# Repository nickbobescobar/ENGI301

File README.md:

# ENGI301
Repository for ENGI 301 coursework

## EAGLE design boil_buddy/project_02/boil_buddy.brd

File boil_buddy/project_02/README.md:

--------------------------------------------------------------------------
Boil Buddy: Text message alerts for a boiling pot of water
--------------------------------------------------------------------------
Copywright 2020 Nicolas Escobar
nick[dot]bob[dot]escobar[at]gmail[dot]com

This is the Boil Buddy PCB Design! Boil Buddy uses a piezoelectric disc to sense vibrations in the pot as water boils and sends a text alert.
This PCB was adapted from a PocketBeagle project and thus makes use of many chips found on that board, including the Octavo Systems OSD353558 Microprocessor.
In converting to the PCB design, my goal was to eliminate extraneous components from the PocketBeagle to cut down on costs and size. However, I learned that
the PocketBeagle doesn't really have much that I don't need built into it (unless I swap the CPU) and that it would be *much* more cost-efficient to make a shield
for the existing board.

The 'boil_buddy' folder on GitHub should contain software used to run the Boil Buddy, at least for the prototyped version. I'm unsure on how to adapt it to a
standalone device, though I figure that I'd be using much of the same Debian backbone because I've kept most of the same hardware.

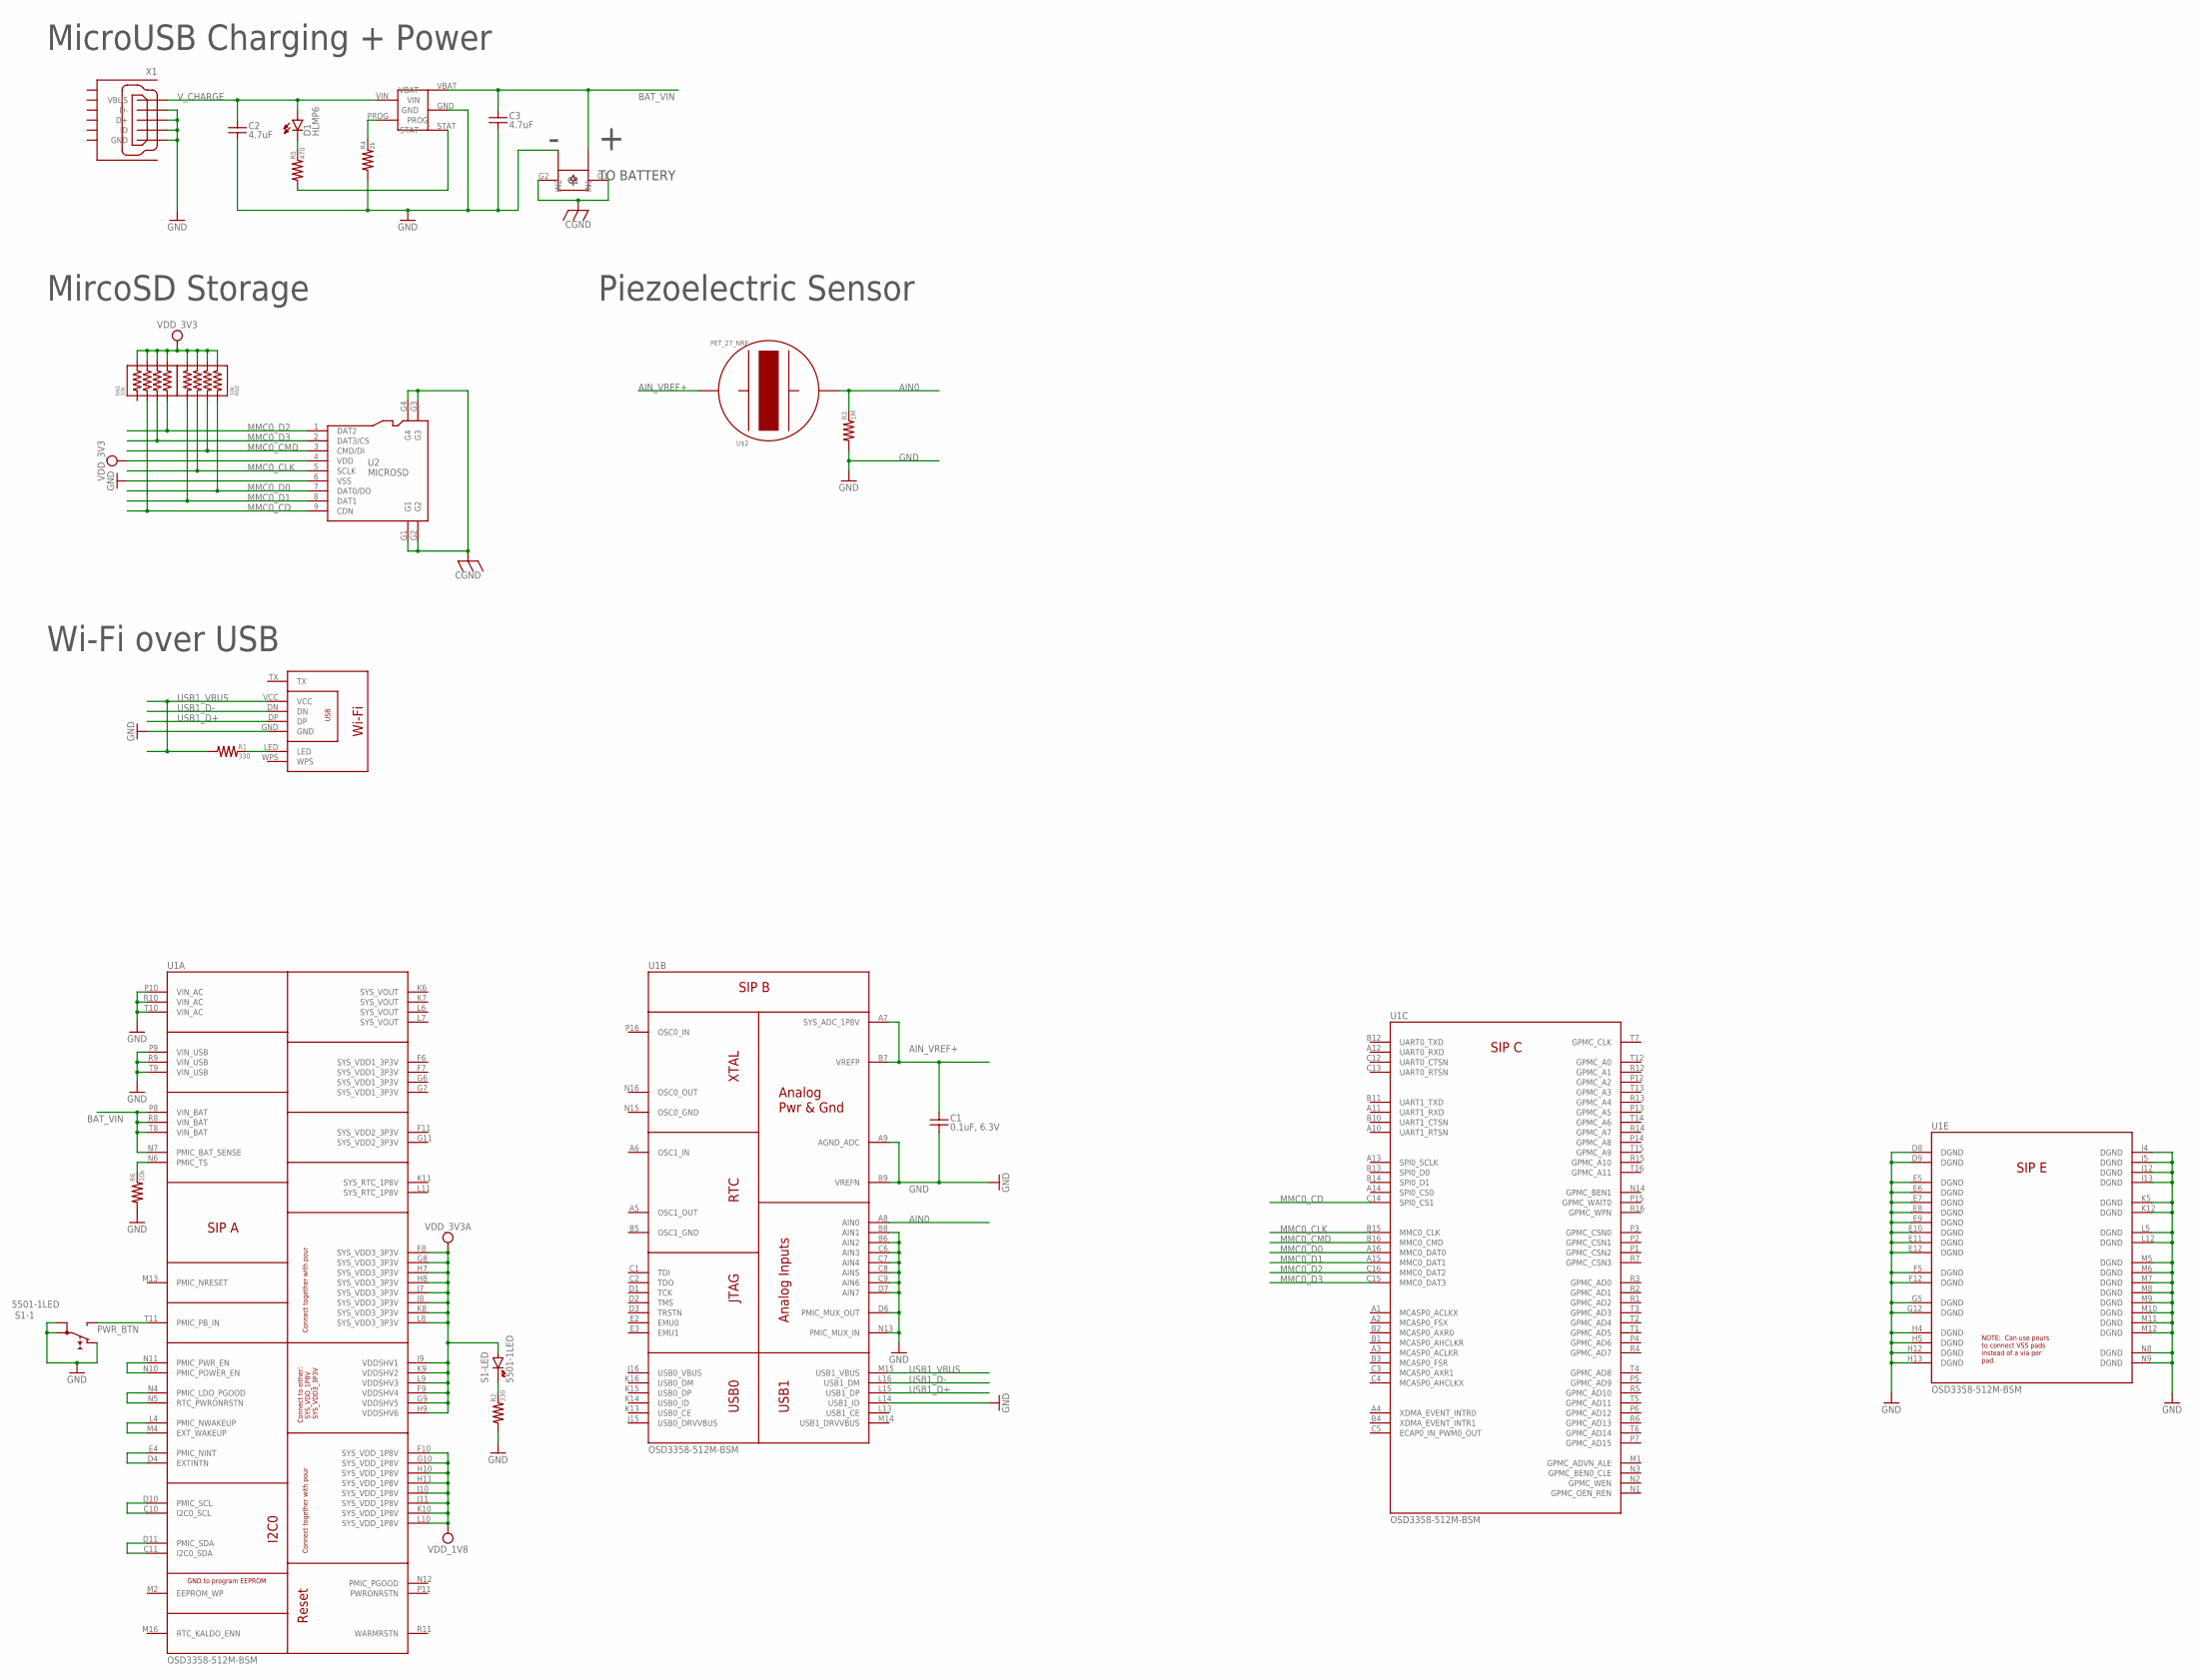
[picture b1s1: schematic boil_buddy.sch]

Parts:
C1: 0.1uF, 6.3V; 0402
C2, C3: 4.7uF; 0603
D1: HLMP6
R1, R2: 330; 0402
R3: 1M; 0402
R4: 2k; 0402
R5: 470; 0402
R6: 10k; 0402
RN1, RN2: 10k; RN0804
S1: 5501-1LED
U1: OSD3358-512M-BSM; OSD335X-BGA-256
U2: MICROSD
U$1: GWF-3M08_NRE; GWF-3M08
U$2: PET_27_NRE; PET_27
U$3: MCP73831_NRE; MCP73831
U$4: 2PIN_NRE; 2PIN
X1: 10118192-0001LF; 10118192-0001LF(MICRO-USB-B-AMPHENOL-FCI)

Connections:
AIN0: R3.2, U1.A8 (AIN0), U$2.PIEZO
AIN_VREF+: C1.1, U1.A7 (SYS_ADC_1P8V), U1.B7 (VREFP), U$2.BRASS
BAT_VIN: C3.1, U1.N7 (PMIC_BAT_SENSE), U1.P8 (VIN_BAT), U1.R8 (VIN_BAT), U1.T8 (VIN_BAT), U$3.VBAT, U$4.IN1
CGND: U2.G1, U2.G2, U2.G3, U2.G4, U$4.G1, U$4.G2
GND: C1.2, C2.2, C3.2, R2.1, R3.1, R4.1, R6.1, S1.1A, S1.1B, S1.NC, U1.A9 (AGND_ADC), U1.B6 (AIN2), U1.B8 (AIN1), U1.B9 (VREFN), U1.C6 (AIN3), U1.C7 (AIN4), U1.C8 (AIN5), U1.C9 (AIN6), U1.D6 (PMIC_MUX_OUT), U1.D7 (AIN7), U1.D8 (DGND), U1.D9 (DGND), U1.E5 (DGND), U1.E6 (DGND), U1.E7 (DGND), U1.E8 (DGND), U1.E9 (DGND), U1.E10 (DGND), U1.E11 (DGND), U1.E12 (DGND), U1.F5 (DGND), U1.F12 (DGND), U1.G5 (DGND), U1.G12 (DGND), U1.H4 (DGND), U1.H5 (DGND), U1.H12 (DGND), U1.H13 (DGND), U1.J4 (DGND), U1.J5 (DGND), U1.J12 (DGND), U1.J13 (DGND), U1.K5 (DGND), U1.K12 (DGND), U1.L5 (DGND), U1.L12 (DGND), U1.L14 (USB1_ID), U1.M5 (DGND), U1.M6 (DGND), U1.M7 (DGND), U1.M8 (DGND), U1.M9 (DGND), U1.M10 (DGND), U1.M11 (DGND), U1.M12 (DGND), U1.N8 (DGND), U1.N9 (DGND), U1.N13 (PMIC_MUX_IN), U1.P9 (VIN_USB), U1.P10 (VIN_AC), U1.R9 (VIN_USB), U1.R10 (VIN_AC), U1.T9 (VIN_USB), U1.T10 (VIN_AC), U2.6 (VSS), U$1.GND, U$3.GND, U$4.IN2, X1.D+, X1.D-, X1.GND, X1.ID
MMC0_CD: RN1.2, U1.C14 (SPI0_CS1), U2.9 (CDN)
MMC0_CLK: RN2.3, U1.B15 (MMC0_CLK), U2.5 (SCLK)
MMC0_CMD: RN2.2, U1.B16 (MMC0_CMD), U2.3 (CMD/DI)
MMC0_D0: RN2.1, U1.A16 (MMC0_DAT0), U2.7 (DAT0/DO)
MMC0_D1: RN2.4, U1.A15 (MMC0_DAT1), U2.8 (DAT1)
MMC0_D2: RN1.4, U1.C16 (MMC0_DAT2), U2.1 (DAT2)
MMC0_D3: RN1.3, U1.C15 (MMC0_DAT3), U2.2 (DAT3/CS)
unnamed: U1.N10 (PMIC_POWER_EN), U1.N11 (PMIC_PWR_EN)
unnamed: U1.N4 (PMIC_LDO_PGOOD), U1.N5 (RTC_PWRONRSTN)
unnamed: U1.L4 (PMIC_NWAKEUP), U1.M4 (EXT_WAKEUP)
unnamed: U1.D4 (EXTINTN), U1.E4 (PMIC_NINT)
unnamed: U1.C10 (I2C0_SCL), U1.D10 (PMIC_SCL)
unnamed: U1.C11 (I2C0_SDA), U1.D11 (PMIC_SDA)
unnamed: R2.2, S1.- (K)
unnamed: R6.2, U1.N6 (PMIC_TS)
unnamed: D1.K, R5.2
unnamed: R5.1, U$3.STAT
unnamed: R1.2, U$1.LED
unnamed: R4.2, U$3.PROG
PWR_BTN: S1.NO, U1.T11 (PMIC_PB_IN)
SYS_RTC_1P8V: U1.K11 (SYS_RTC_1P8V), U1.L11 (SYS_RTC_1P8V)
SYS_VDD1_3P3V: U1.F6 (SYS_VDD1_3P3V), U1.F7 (SYS_VDD1_3P3V), U1.G6 (SYS_VDD1_3P3V), U1.G7 (SYS_VDD1_3P3V)
SYS_VDD2_3P3V: U1.F11 (SYS_VDD2_3P3V), U1.G11 (SYS_VDD2_3P3V)
SYS_VOUT: U1.K6 (SYS_VOUT), U1.K7 (SYS_VOUT), U1.L6 (SYS_VOUT), U1.L7 (SYS_VOUT)
USB1_D+: U1.L15 (USB1_DP), U$1.DP
USB1_D-: U1.L16 (USB1_DM), U$1.DN
USB1_VBUS: R1.1, U1.M15 (USB1_VBUS), U$1.VCC
VDD_1V8: U1.F10 (SYS_VDD_1P8V), U1.G10 (SYS_VDD_1P8V), U1.H10 (SYS_VDD_1P8V), U1.H11 (SYS_VDD_1P8V), U1.J10 (SYS_VDD_1P8V), U1.J11 (SYS_VDD_1P8V), U1.K10 (SYS_VDD_1P8V), U1.L10 (SYS_VDD_1P8V)
VDD_3V3A: RN1.5, RN1.6, RN1.7, RN1.8, RN2.5, RN2.6, RN2.7, RN2.8, S1.+ (A), U1.F8 (SYS_VDD3_3P3V), U1.F9 (VDDSHV4), U1.G8 (SYS_VDD3_3P3V), U1.G9 (VDDSHV5), U1.H7 (SYS_VDD3_3P3V), U1.H8 (SYS_VDD3_3P3V), U1.H9 (VDDSHV6), U1.J7 (SYS_VDD3_3P3V), U1.J8 (SYS_VDD3_3P3V), U1.J9 (VDDSHV1), U1.K8 (SYS_VDD3_3P3V), U1.K9 (VDDSHV2), U1.L8 (SYS_VDD3_3P3V), U1.L9 (VDDSHV3), U2.4 (VDD)
V_CHARGE: C2.1, D1.A, U$3.VIN, X1.VBUS

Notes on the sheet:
TO BATTERY
MicroUSB Charging + Power
MircoSD Storage
Wi-Fi over USB
Piezoelectric Sensor

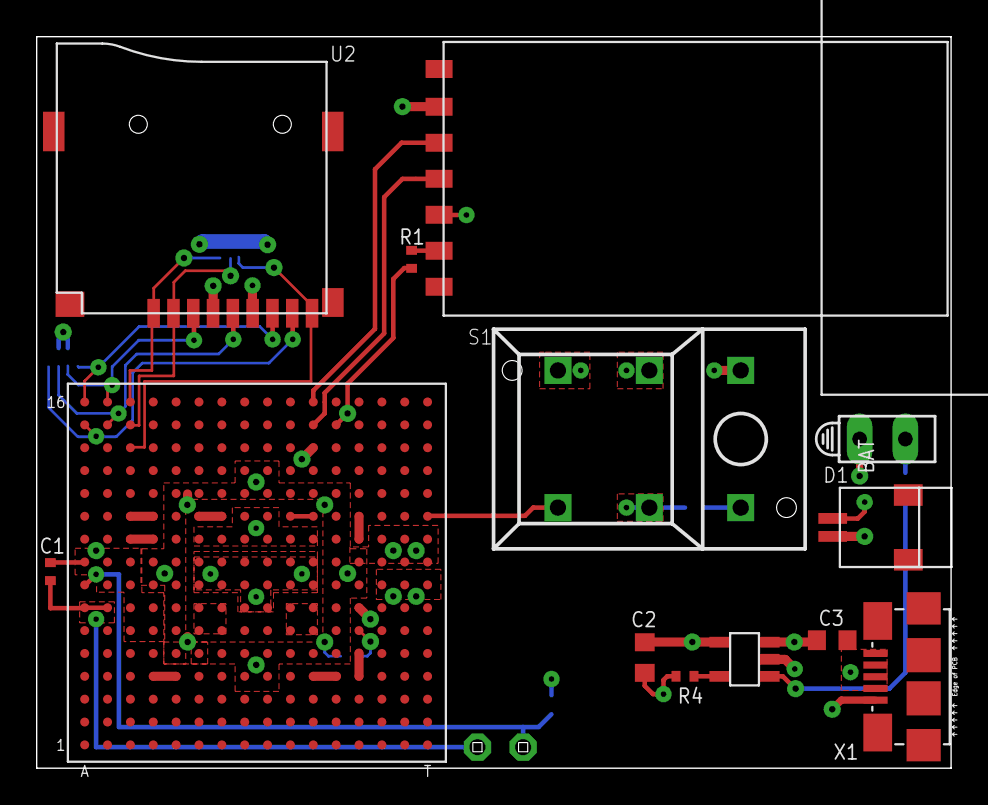
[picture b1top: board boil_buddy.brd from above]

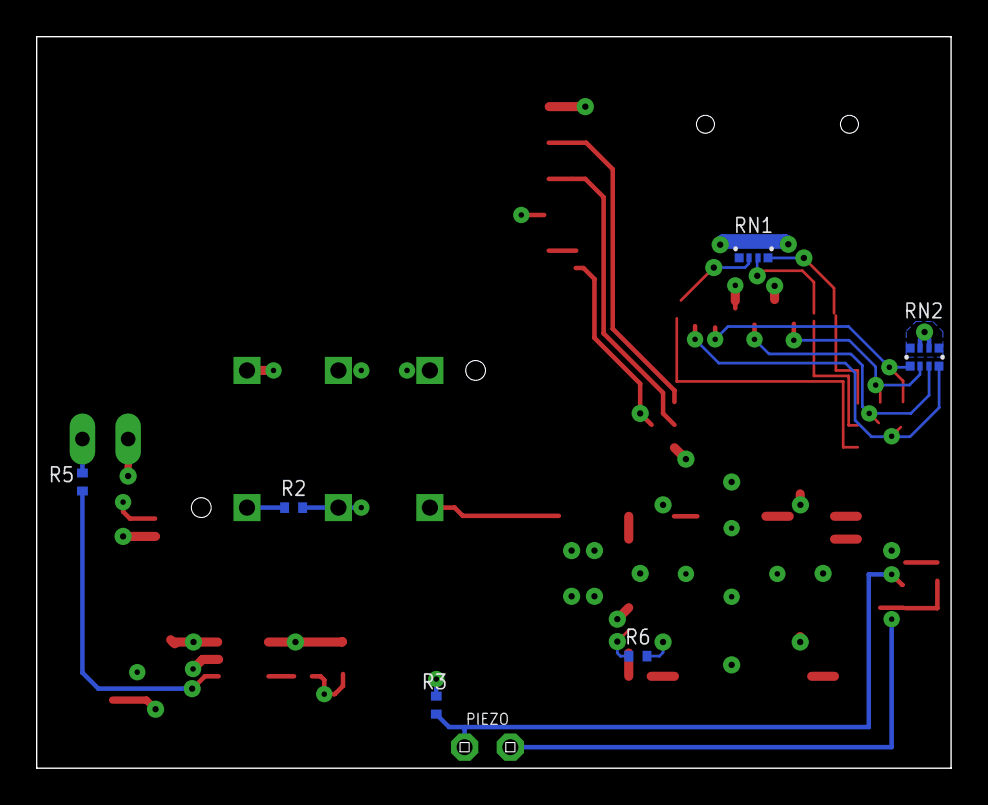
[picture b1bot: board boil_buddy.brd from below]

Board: 4 copper layers, 50.8 x 40.6 mm, 20 parts (7 on the bottom side), 35 nets.

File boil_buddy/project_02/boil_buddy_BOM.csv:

Designator,Manufacturer,Quantity,Description,Datasheet
"330? Resistor, 0402",,2,Basic SMD resistors,
"470? Resistor, 0402",,2,Basic SMD resistors,
"2k? Resistor, 0402",,1,Basic SMD resistors,
"10k? Resistor, 0402",,1,Basic SMD resistors,
"1M? Resistor, 0402",,1,Basic SMD resistors,
"0.1uF Capacitor, 0402",,1,Basic SMD ceramic capacitors,
"4.7uF Capacitor, 0603",,2,Basic SMD ceramic capacitors,
4x10k? Resistor Network,,2,Basic SMD resistors,
PET27_NRE,TIMESETL,1,27mm Piezoelectric Sensor Disc,https://www.amazon.com/dp/B077YJ3H6R
MCP73831,Microchip,1,"Single Cell, Li-Ion/Li-Polymer Charge Management Controller",https://ww1.microchip.com/downloads/en/DeviceDoc/MCP73831-Fa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
MICROSD,,1,MicroSD card slot,
2PIN_NRE,JST Sales America,1,"SHR-02V-S 2 Pin connector, used for battery",http://www.jst-mfg.com/product/pdf/eng/eSH.pdf
OSD3358-512M-BSM,Octavo Systems,1,Octavo OSD3358 Microprocessor,https://octavosystems.com/docs/osd335x-sm-datasheet/
GWF-3M08_NRE,ACME Systems,1,WIFI-2 over USB Module,https://www.acmesystems.it/www/WIFI-2/GWF-3M08-Datasheet.pdf
5501-1LED,E-Switch,1,PUSHBUTTON SERIES 5500 SWITCHES 1 LED,https://sten-eswitch-13110800-production.s3.amazonaws.com/sy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
HLMP-6000,Broadcom,1,Hole-mounted LED,https://docs.broadcom.com/doc/AV02-1496EN
10118192-0001LF,Amphenol ICC,1,Micro USB Type B Complete Surface Mount (SMT) no guide holes,https://cdn.amphenol-icc.com/media/wysiwyg/files/documentati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
HPL402323-2C-190mAh,Hypercell,1,Li-ion Polymer Battery 190mAh,https://download.mikroe.com/documents/datasheets/HPL402323-2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

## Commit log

2020-09-16 Update README.md
    Updating README.md
2020-09-29 -adding files I forgot to track earlier: assignment_04, mmap -new python folder with simple_calc.py -simple_calc.py can do basic math ops and move your answer forward, with data validation
2020-09-29 Added. Can't get keyboard control to work.
2020-09-30 uploaded blink_USR3.py
2020-11-14 Add files via upload
    Added Boil Buddy python project files.
2020-11-14 Add files via upload
    Added MATLAB for Boil Buddy
2020-11-14 Add files via upload
    Added README
2020-11-14 Add files via upload
    updated readme
2020-11-14 Add files via upload
    Fritzing, MATLAB
2020-12-19 Boil Buddy PCB
